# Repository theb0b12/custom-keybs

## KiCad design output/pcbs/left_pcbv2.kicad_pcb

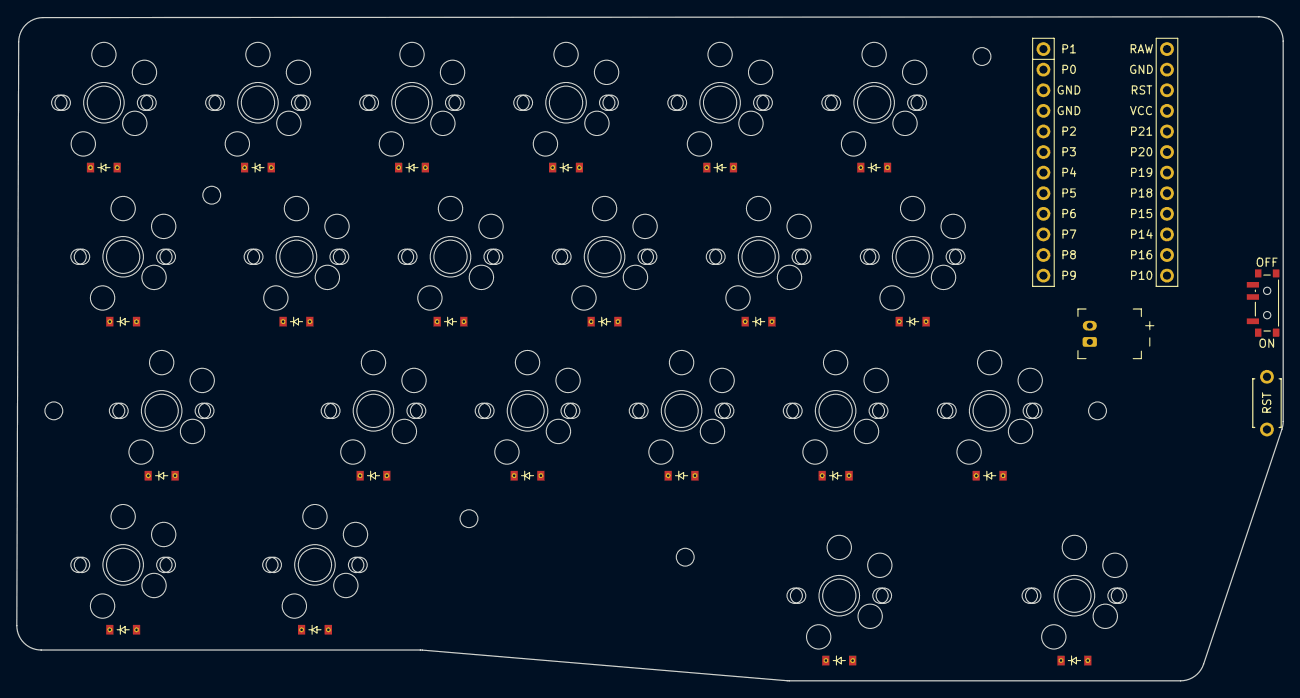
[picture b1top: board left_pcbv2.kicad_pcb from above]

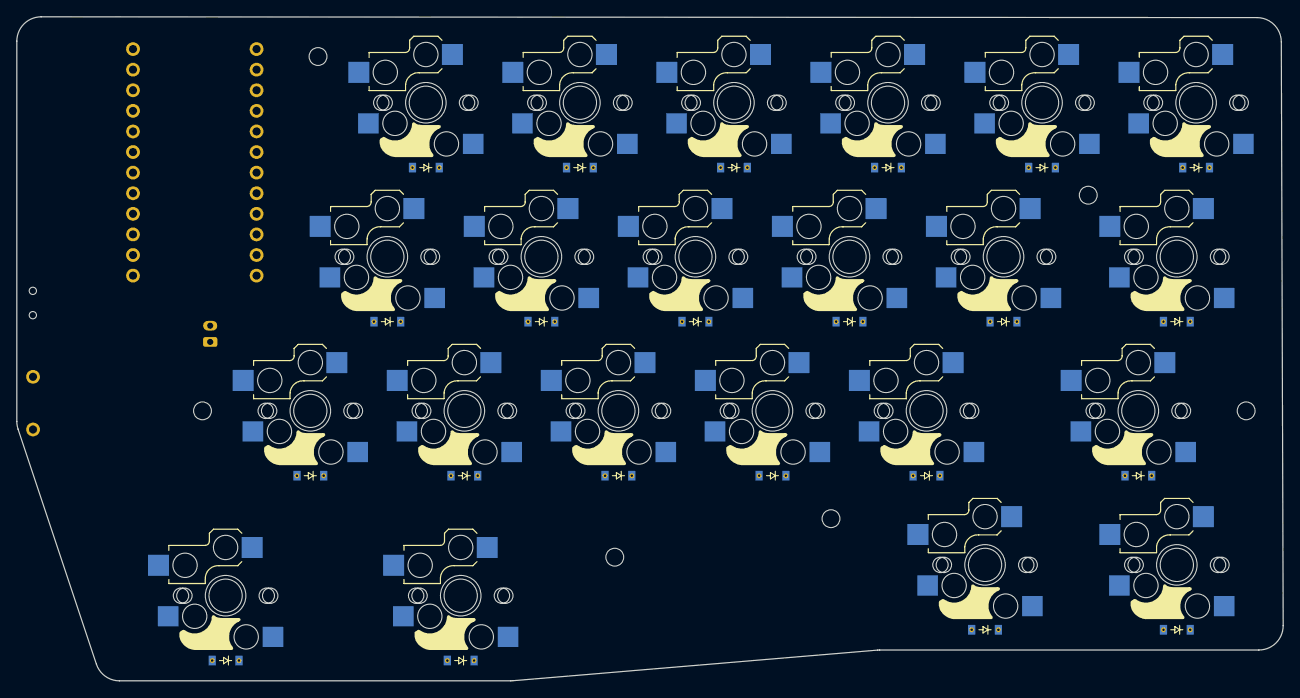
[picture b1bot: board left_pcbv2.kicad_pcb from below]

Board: 2 copper layers, 156.2 x 81.9 mm, 76 parts (44 on the bottom side), 36 nets, no tracks yet.

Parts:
D1, D2, D3, D4, D5, D6, D7, D8, D9, D10, D11, D12, D13, D14, D15, D16, D17, D18, D19, D20, D21, D22: ComboDiode
JST1: battery_connector_jst_ph_2
MCU1: mcu_nice_nano
MH1, MH2, MH3, MH4, MH5, MH6: mounting_hole_npth
PWR1: power_switch_smd_side
RST1: reset_switch_tht_top
S1, S2, S3, S4, S5, S6, S7, S8, S9, S10, S11, S12, S13, S14, S15, S16, S17, S18, S19, S20, S21, S22: switch_choc_v1_v2
S23, S24, S25, S26, S27, S28, S29, S30, S31, S32, S33, S34, S35, S36, S37, S38, S39, S40, S41, S42, S43, S44: switch_mx

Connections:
BAT_P: JST1.2, PWR1.1
GND: JST1.1, MCU1.2, MCU1.21, MCU1.22, RST1.2
P0: MCU1.23, S1.1, S7.1, S13.1, S19.1, S23.1, S29.1, S35.1, S41.1
P1: MCU1.24, S2.1, S8.1, S14.1, S20.1, S24.1, S30.1, S36.1, S42.1
P2: MCU1.20, S3.1, S9.1, S15.1, S25.1, S31.1, S37.1
P3: MCU1.19, S4.1, S10.1, S16.1, S26.1, S32.1, S38.1
P4: MCU1.18, S5.1, S11.1, S17.1, S27.1, S33.1, S39.1
P5: MCU1.17, S6.1, S12.1, S18.1, S21.1, S22.1, S28.1, S34.1, S40.1, S43.1, S44.1
P6: D1.1, D2.1, D3.1, D4.1, D5.1, D6.1, MCU1.16
P7: D7.1, D8.1, D9.1, D10.1, D11.1, D12.1, MCU1.15
P8: D13.1, D14.1, D15.1, D16.1, D17.1, D18.1, MCU1.14
P9: D19.1, D20.1, D21.1, D22.1, MCU1.13
RAW: MCU1.1, PWR1.2
RST: MCU1.3, RST1.1
a_default: D8.1, D8.2, S8.2, S30.2
b_default: D18.1, D18.2, S18.2, S40.2
c_default: D16.1, D16.2, S16.2, S38.2
d_default: D10.1, D10.2, S10.2, S32.2
e_default: D4.1, D4.2, S4.2, S26.2
esc_default: D1.1, D1.2, S1.2, S23.2
f_default: D11.1, D11.2, S11.2, S33.2
g_default: D12.1, D12.2, S12.2, S34.2
lctrl_default: D19.1, D19.2, S19.2, S41.2
lower_default: D21.1, D21.2, S21.2, S43.2
lshift_default: D13.1, D13.2, S13.2, S35.2
q_default: D2.1, D2.2, S2.2, S24.2
r_default: D5.1, D5.2, S5.2, S27.2
s_default: D9.1, D9.2, S9.2, S31.2
space_default: D22.1, D22.2, S22.2, S44.2
super_default: D20.1, D20.2, S20.2, S42.2
t_default: D6.1, D6.2, S6.2, S28.2
tab_default: D7.1, D7.2, S7.2, S29.2
v_default: D17.1, D17.2, S17.2, S39.2
w_default: D3.1, D3.2, S3.2, S25.2
x_default: D15.1, D15.2, S15.2, S37.2
z_default: D14.1, D14.2, S14.2, S36.2

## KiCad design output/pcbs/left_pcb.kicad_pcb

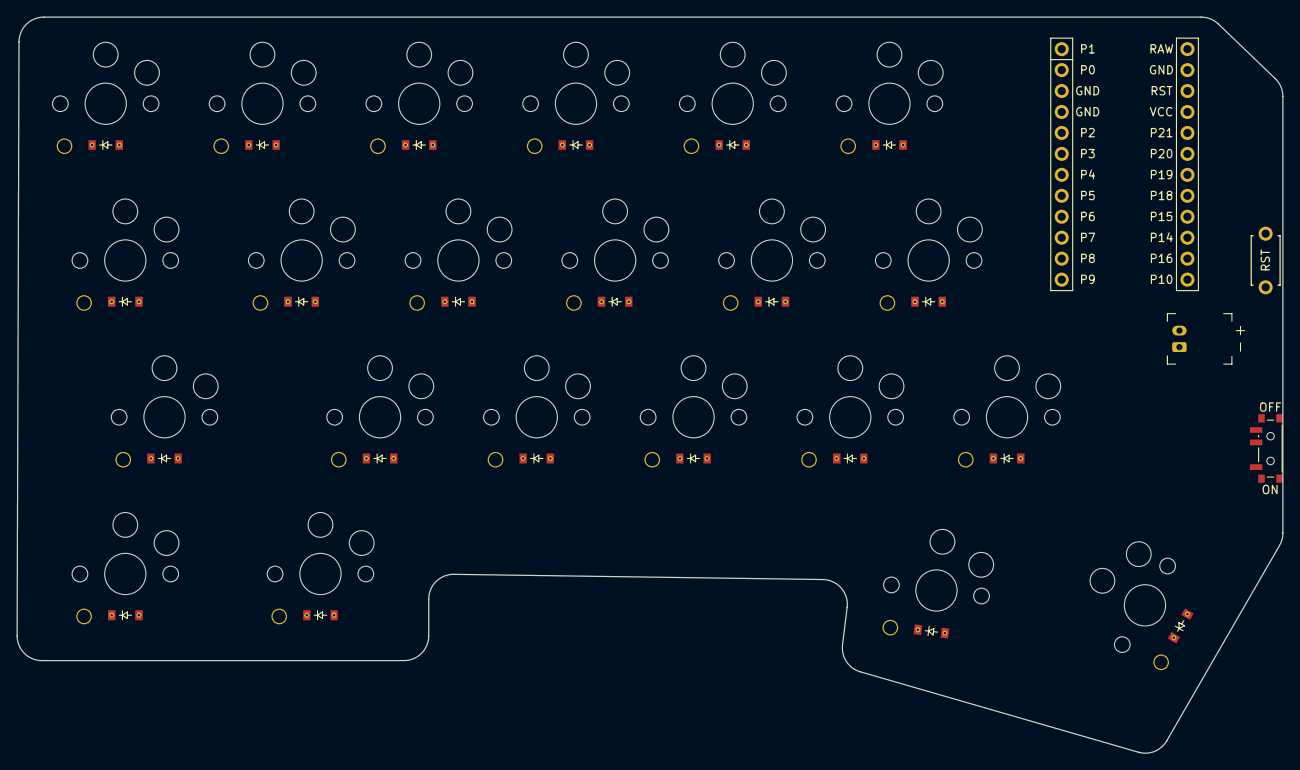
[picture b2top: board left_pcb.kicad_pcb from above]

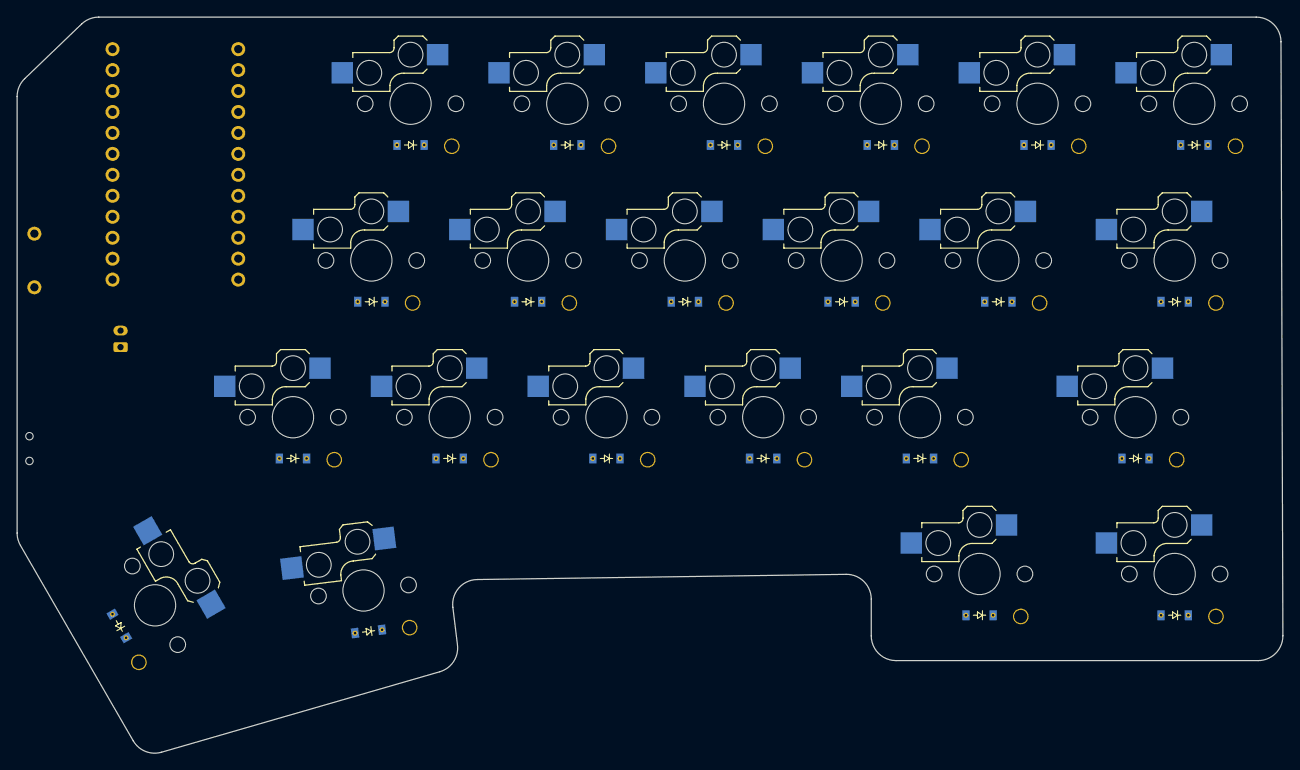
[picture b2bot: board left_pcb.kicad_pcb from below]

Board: 2 copper layers, 153.4 x 89.2 mm, 48 parts (22 on the bottom side), 36 nets, no tracks yet.

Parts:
D1, D2, D3, D4, D5, D6, D7, D8, D9, D10, D11, D12, D13, D14, D15, D16, D17, D18, D19, D20, D21, D22: ComboDiode
JST1: battery_connector_jst_ph_2
MCU1: mcu_nice_nano
PWR1: power_switch_smd_side
RST1: reset_switch_tht_top
S1, S2, S3, S4, S5, S6, S7, S8, S9, S10, S11, S12, S13, S14, S15, S16, S17, S18, S19, S20, S21, S22: switch_choc_v1_v2

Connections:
BAT_P: JST1.2, PWR1.1
GND: JST1.1, MCU1.2, MCU1.21, MCU1.22, RST1.2
P0: MCU1.23, S1.1, S7.1, S13.1, S19.1
P1: MCU1.24, S2.1, S8.1, S14.1, S20.1
P2: MCU1.20, S3.1, S9.1, S15.1
P3: MCU1.19, S4.1, S10.1, S16.1
P4: MCU1.18, S5.1, S11.1, S17.1
P5: MCU1.17, S6.1, S12.1, S18.1, S21.1, S22.1
P6: D1.1, D2.1, D3.1, D4.1, D5.1, D6.1, MCU1.16
P7: D7.1, D8.1, D9.1, D10.1, D11.1, D12.1, MCU1.15
P8: D13.1, D14.1, D15.1, D16.1, D17.1, D18.1, MCU1.14
P9: D19.1, D20.1, D21.1, D22.1, MCU1.13
RAW: MCU1.1, PWR1.2
RST: MCU1.3, RST1.1
a_default: D8.1, D8.2, S8.2
b_default: D18.1, D18.2, S18.2
c_default: D16.1, D16.2, S16.2
d_default: D10.1, D10.2, S10.2
e_default: D4.1, D4.2, S4.2
esc_default: D1.1, D1.2, S1.2
f_default: D11.1, D11.2, S11.2
g_default: D12.1, D12.2, S12.2
lctrl_default: D19.1, D19.2, S19.2
lower_default: D21.1, D21.2, S21.2
lshift_default: D13.1, D13.2, S13.2
q_default: D2.1, D2.2, S2.2
r_default: D5.1, D5.2, S5.2
s_default: D9.1, D9.2, S9.2
space_default: D22.1, D22.2, S22.2
super_default: D20.1, D20.2, S20.2
t_default: D6.1, D6.2, S6.2
tab_default: D7.1, D7.2, S7.2
v_default: D17.1, D17.2, S17.2
w_default: D3.1, D3.2, S3.2
x_default: D15.1, D15.2, S15.2
z_default: D14.1, D14.2, S14.2

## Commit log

2026-01-17 anotha one
2026-01-17 ergogen installed
2026-01-17 random error stuff for silly me trying to do npm install
2026-01-17 board finished kinda
2026-01-17 Swap keys 'tab' and 'esc' in config1.yaml
2026-01-17 Modify thumbfan shifts and add outlines
    Updated thumbfan shift values and added outlines for keycaps and board.
2026-01-18 easy commit
2026-01-18 something idk
2026-01-18 made the thumbfan more cornelike and changed the left side to be smaller
2026-01-18 random stuff
2026-01-18 Add outlines configuration
    Added new outline definitions for raw, keys, board, and combo.
2026-01-18 anathaone
2026-01-18 removed extranious stuff
2026-01-18 Add .mcp.json to .gitignore
    made a gitignore
2026-01-22 changed some stuff around idk
2026-01-22 removed node moduals becasue its not needed
2026-01-22 split the board and changed the key widths for the first column left side
2026-01-25 left side pcb, n!n, battery connector, on off, and reset
2026-01-29 started doing the goofy ah nets, top row done
2026-01-29 finished left side pcb???? def not
2026-01-29 addedceoloide and smd diode
2026-01-29 moved some stuiff
2026-01-31 idk commits
2026-02-01 Add rectangle definition for r5_super in keys dxf
2026-02-01 Adjust shift values and cleaned up outlines section
2026-02-01 Refactor bothsides.yaml by removing board_right
    Removed the 'board_right' configuration and updated the 'combo' section.
2026-02-01 something night of the day commit
2026-02-01 added solidworks case file
2026-02-02 added pcb thing
2026-02-03 right side mx switches and row and column nets
2026-02-03 something else idk
2026-02-03 made rows maybe work
2026-02-04 right side changes like mx switch
2026-02-04 updated left side
2026-02-04 some changes that idk
2026-02-04 some other commits
2026-02-04 pcbs finished for now
2026-02-05 added maybe a correct switch plate
2026-02-05 added case things
2026-02-05 made switchplatetesters better
2026-02-06 mounting holes and case left side
2026-02-06 mounting holes for left pcb
2026-02-07 left pcb route and finished the mounting holes for pcb and case
2026-02-08 moved spacebar around
2026-02-09 fixed stuff idk allot
2026-02-09 made bothsides yaml up to date and gened svg for keymap
2026-02-09 anather one
2026-02-12 case change smth
2026-02-12 useless thing idk
2026-02-27 smth idrk anymore
2026-02-27 keymap
2026-02-27 updated keymap.json
2026-03-01 updated smth
2026-03-07 added photos
